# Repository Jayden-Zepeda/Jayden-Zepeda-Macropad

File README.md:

# ZepedaPad

> A custom 14-key macropad with dual rotary encoders, per-key RGB lighting, and an OLED display — built on the Seeed XIAO RP2040 with QMK firmware.

---

## 📖 Overview

The **Zepeda** is a compact, handcrafted macropad designed for productivity and personalization. It features 14 MX-style switches arranged in a 3×4 grid (plus a dedicated column), two EC11 rotary encoders for scrolling or volume control, individually addressable SK6812 MINI-E RGB LEDs under every key, and a 0.91" OLED display for live feedback — all driven by a Seeed XIAO RP2040 and QMK firmware.

The key matrix is read through a **74HC165 shift register**, keeping GPIO usage minimal while supporting full anti-ghosting via 1N4148 diodes. The entire build fits inside a custom 3-part 3D-printed case secured with heatset inserts and M3 screws.

PCB is designed through KICAD and the case is designed in Autodesk Fusion-FREE.

---

## 🖼️ Screenshots

### 3D Render

<p align="center">
  
  <br/><em>Top-down view</em>
</p>

<p align="center">
  
  <br/><em>Isometric view showing case depth and USB cutout</em>
</p>

---

### Schematic

> Full schematic showing the XIAO RP2040, 74HC165 shift register, LED chain, diode matrix, rotary encoders, and OLED connector.

<p align="center">
  
  <br/><em>KiCad schematic — macropad.kicad_sch</em>
</p>

---

### PCB Layout

<p align="center">
  
  <br/><em>KiCad PCB layout — red/blue layers, switch footprints, and LED positions visible</em>
</p>

---

### Case

<p align="center">
  
  <br/><em>3-part 3D-printed enclosure with heatset inserts. The PCB sits inside the bottom shell; the top plate exposes keycaps, encoders, and the OLED. A middle layer sandwiches everything together. Screws are enter from bottom, they go in 2mm freely and then left side screws all the way into the heatset insterts that are in the top shell while, the right side screws does a very similar thing except the heatset insterts are 1mm in the top shell and 3mm in the middle shell.</em>
</p>

The case consists of three printed parts(created in Autodesk Fusion-FREE) :
- **Bottom shell** — holds the PCB
- **Middle frame / plate** — key switch mounting plate
- **Top accent** — surrounds the OLED and encoder knobs

All three parts are secured with **4× M3×16mm screws** threading into **4× M3×5mm×4mm heatset inserts** pressed into the top/middle shell.

---

## 🧰 Bill of Materials (BOM)

| Qty | Part | Notes |
|-----|------|-------|
| 1 | Seeed XIAO RP2040 | Microcontroller (unsoldered) |
| 1 | 74HC165 Shift Register | Through-hole DIP-16 |
| 16 | SK6812 MINI-E LEDs | Per-key addressable RGB |
| 16 | 1N4148 Diodes | Through-hole, for key matrix |
| 14 | MX-Style Switches | Any MX-compatible switch |
| 14 | White Blank DSA Keycaps | 1u, blank |
| 2 | EC11 Rotary Encoders | With push-click |
| 1 | 0.91" OLED Display | I2C, SSD1306 |
| 1 | 3D-Printed Case | 3 printed parts |
| 4 | M3×16mm Screws | Case assembly |
| 4 | M3×5mm×4mm Heatset Inserts | Press-fit into top/middle shell |

---

## ⚡ Firmware

This macropad runs **QMK Firmware**. The 74HC165 shift register is used to read the key matrix, and the SK6812 MINI-E LEDs are driven via QMK's RGB Matrix feature. Created a full keyboard and keymap layout from scratch. Included in firmware folder(macropad).                                    

Features:
-Copy/Paste Key: First click is copy-second is paste, with an led and OLED display to show your status.
-Mute/Unmute Key: Led and OLED display to show your status
-4 Different Layers: Base, Media, Gaming, and CFG -- w/ led status

To build and flash:

```bash
qmk compile -kb macropad -km default
qmk flash -kb macropad -km default
```

Put the XIAO RP2040 into bootloader mode by holding **BOOT** while plugging in USB (or double-tapping RST).

---

## 🔧 Build Notes

- Solder **heatset inserts first** before assembling the case
- Flash QMK firmware onto the XIAO RP2040 **before** soldering it to the board
- The LED chain is daisy-chained: DOUT of each SK6812 connects to DIN of the next
- Diodes are oriented with the **cathode (K) toward the row line** — check markings before soldering
- The 74HC165's `~PL`, `CP`, and `Q7` lines connect to GPIO26, GPIO27, and GPIO28 on the XIAO respectively

---

## 📁 Repository Structure

```
Jayden-Zepeda-Macropad/
├── pcb/               # KiCad project files (.kicad_sch, .kicad_pcb)
├── case/              # 3D print files (.step / .stl)
├── firmware/          # QMK keymap and config
├── images/            # Images
├── production/            # Files for production
└── README.md
```

---

*Made with ❤️ as part of [Hack Club's PCB program](https://hackclub.com/)*

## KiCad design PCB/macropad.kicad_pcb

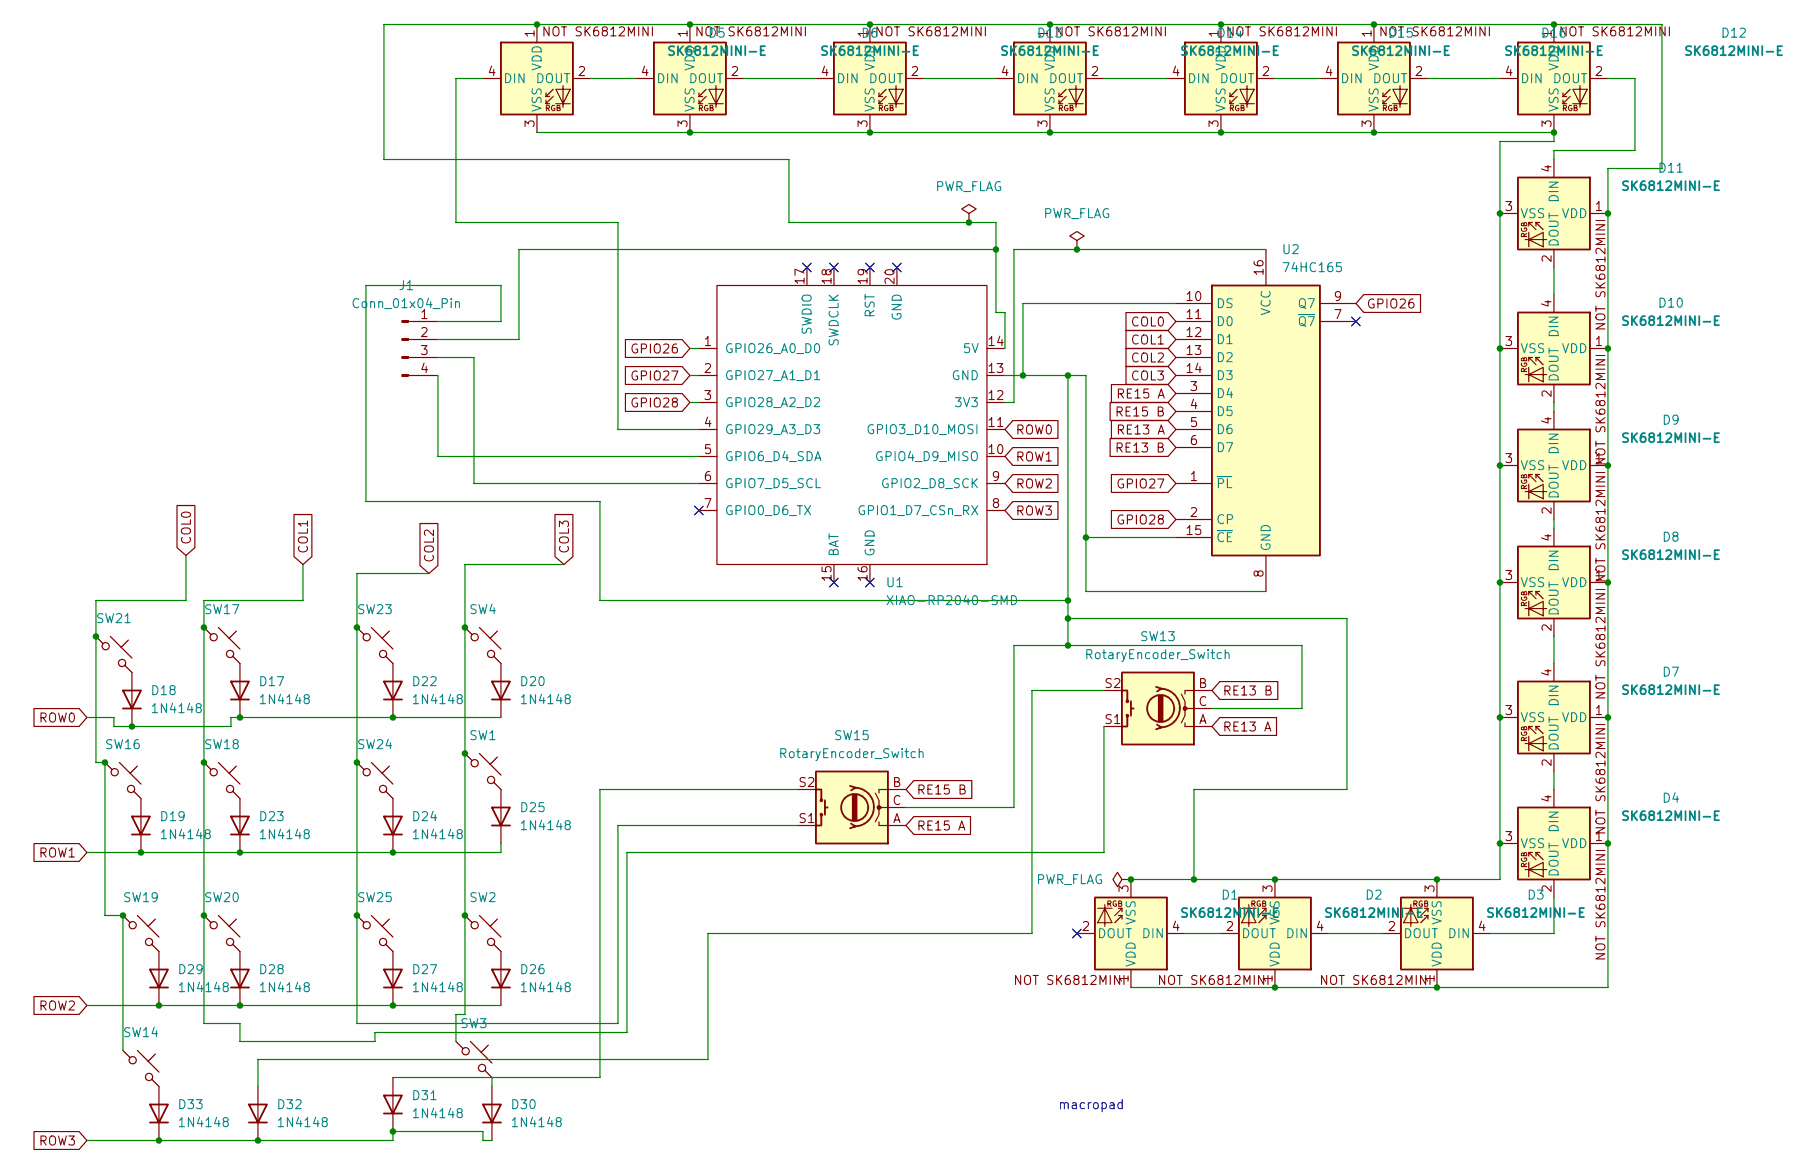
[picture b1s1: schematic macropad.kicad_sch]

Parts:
D1, D2, D3, D4, D5, D6, D7, D8, D9, D10, D11, D12, D13, D14, D15, D16: SK6812MINI-E; LED_SK6812MINI_PLCC4_3.5x3.5mm_P1.75mm
D17, D18, D19, D20, D22, D23, D24, D25, D26, D27, D28, D29, D30, D31, D32, D33: 1N4148; D_DO-35_SOD27_P7.62mm_Horizontal
J1: Conn_01x04_Pin; PinHeader_1x04_P2.54mm_Vertical
SW1, SW2, SW3, SW4, SW16, SW17, SW18, SW19, SW20, SW21, SW23, SW24, SW25: SW_Push_45deg; SW_Cherry_MX_1.00u_PCB
SW13, SW15: RotaryEncoder_Switch; RotaryEncoder_Alps_EC11E-Switch_Vertical_H20mm
SW14: SW_Push_45deg; SW_Cherry_MX_2.00u_PCB
U1: XIAO-RP2040-SMD; XIAO-RP2040-DIP
U2: 74HC165; DIP254P762X420-16

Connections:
COL0: SW14.1, SW16.1, SW19.1, SW21.1, U2.11 (D0)
COL1: SW13.S1, SW17.1, SW18.1, SW20.1, U2.12 (D1)
COL2: SW15.S1, SW23.1, SW24.1, SW25.1, U2.13 (D2)
COL3: SW1.1, SW2.1, SW3.1, SW4.1, U2.14 (D3)
GPIO26: U1.1 (GPIO26_A0_D0), U2.9 (Q7)
GPIO27: U1.2 (GPIO27_A1_D1), U2.1 (~PL)
GPIO28: U1.3 (GPIO28_A2_D2), U2.2 (CP)
unnamed: D1.4 (DIN), D2.2 (DOUT)
unnamed: D1.1 (VDD), D2.1 (VDD), D3.1 (VDD), D4.1 (VDD), D5.1 (VDD), D6.1 (VDD), D7.1 (VDD), D8.1 (VDD), D9.1 (VDD), D10.1 (VDD), D11.1 (VDD), D12.1 (VDD), D13.1 (VDD), D14.1 (VDD), D15.1 (VDD), D16.1 (VDD), J1.2, U1.14 (5V)
unnamed: D1.3 (VSS), D2.3 (VSS), D3.3 (VSS), D4.3 (VSS), D5.3 (VSS), D6.3 (VSS), D7.3 (VSS), D8.3 (VSS), D9.3 (VSS), D10.3 (VSS), D11.3 (VSS), D12.3 (VSS), D13.3 (VSS), D14.3 (VSS), D15.3 (VSS), D16.3 (VSS), J1.1, SW13.C, SW15.C, U1.13 (GND), U2.8 (GND), U2.10 (DS), U2.15 (~CE)
unnamed: D2.4 (DIN), D3.2 (DOUT)
unnamed: D3.4 (DIN), D4.2 (DOUT)
unnamed: D4.4 (DIN), D7.2 (DOUT)
unnamed: D5.4 (DIN), U1.4 (GPIO29_A3_D3)
unnamed: D5.2 (DOUT), D6.4 (DIN)
unnamed: D7.4 (DIN), D8.2 (DOUT)
unnamed: D8.4 (DIN), D9.2 (DOUT)
unnamed: D10.4 (DIN), D11.2 (DOUT)
unnamed: D9.4 (DIN), D10.2 (DOUT)
unnamed: D11.4 (DIN), D12.2 (DOUT)
unnamed: D12.4 (DIN), D16.2 (DOUT)
unnamed: D6.2 (DOUT), D13.4 (DIN)
unnamed: D13.2 (DOUT), D14.4 (DIN)
unnamed: D14.2 (DOUT), D15.4 (DIN)
unnamed: D15.2 (DOUT), D16.4 (DIN)
unnamed: D17.2 (A), SW17.2
unnamed: D18.2 (A), SW21.2
unnamed: D19.2 (A), SW16.2
unnamed: D20.2 (A), SW4.2
unnamed: D22.2 (A), SW23.2
unnamed: D23.2 (A), SW18.2
unnamed: D24.2 (A), SW24.2
unnamed: D25.2 (A), SW1.2
unnamed: D26.2 (A), SW2.2
unnamed: D27.2 (A), SW25.2
unnamed: D28.2 (A), SW20.2
unnamed: D29.2 (A), SW19.2
unnamed: D30.2 (A), SW3.2
unnamed: D31.2 (A), SW15.S2
unnamed: D32.2 (A), SW13.S2
unnamed: D33.2 (A), SW14.2
unnamed: J1.3, U1.6 (GPIO7_D5_SCL)
unnamed: J1.4, U1.5 (GPIO6_D4_SDA)
unnamed: U1.12 (3V3), U2.16 (VCC)
RE13 A: SW13.A, U2.5 (D6)
RE13 B: SW13.B, U2.6 (D7)
RE15 A: SW15.A, U2.3 (D4)
RE15 B: SW15.B, U2.4 (D5)
ROW0: D17.1 (K), D18.1 (K), D20.1 (K), D22.1 (K), U1.11 (GPIO3_D10_MOSI)
ROW1: D19.1 (K), D23.1 (K), D24.1 (K), D25.1 (K), U1.10 (GPIO4_D9_MISO)
ROW2: D26.1 (K), D27.1 (K), D28.1 (K), D29.1 (K), U1.9 (GPIO2_D8_SCK)
ROW3: D30.1 (K), D31.1 (K), D32.1 (K), D33.1 (K), U1.8 (GPIO1_D7_CSn_RX)

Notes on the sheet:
macropad

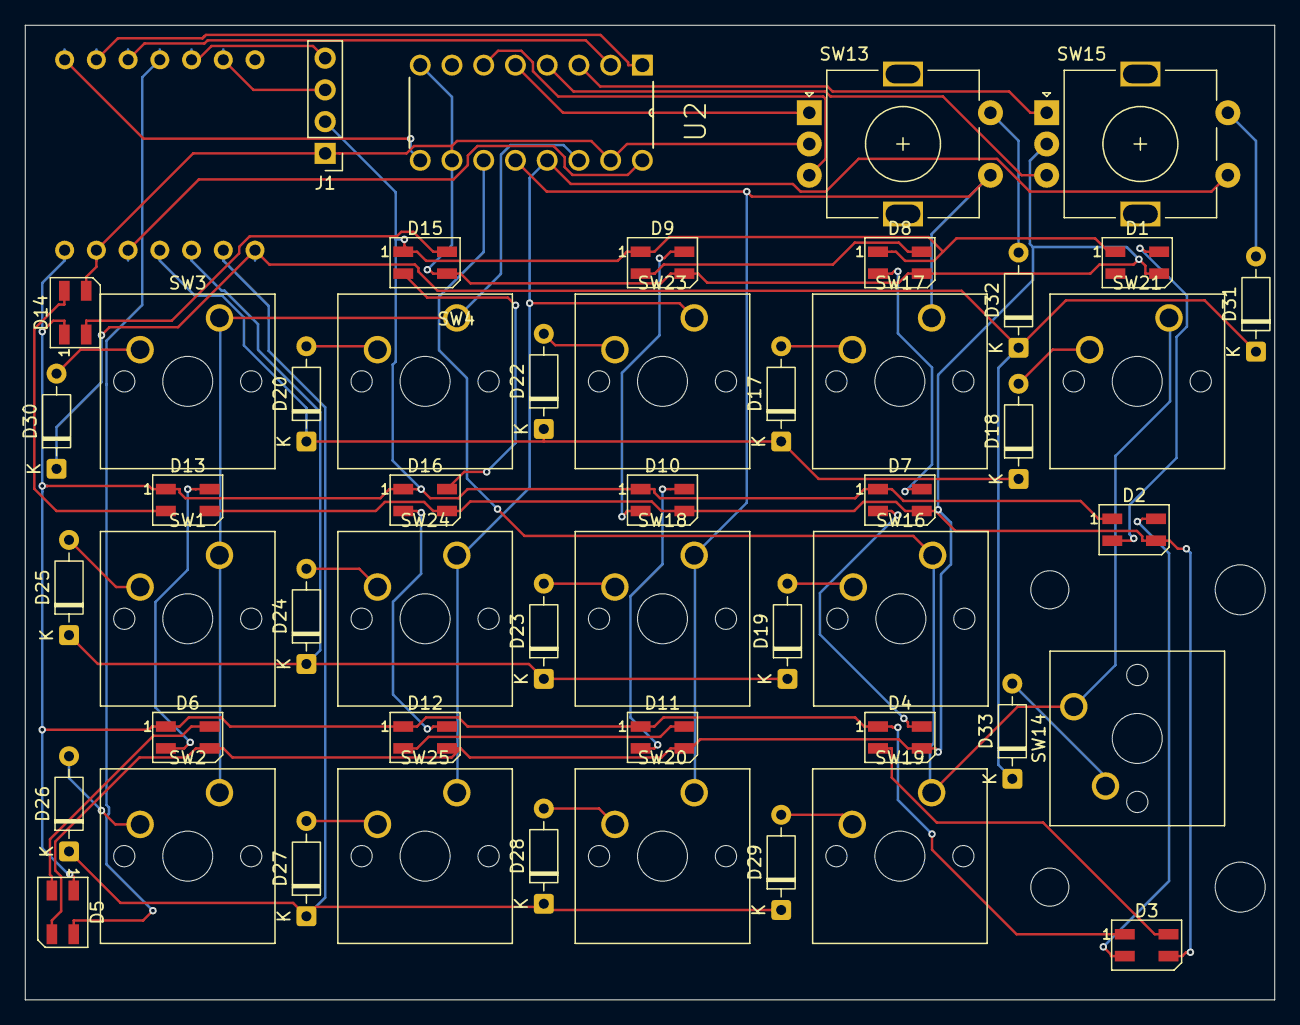
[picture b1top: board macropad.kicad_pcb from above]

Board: 2 copper layers, 100.0 x 78.0 mm, 51 parts (1 on the bottom side), 52 nets.

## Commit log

2026-03-30 Firmware and Production is left
2026-03-30 Almost done- REVIEW NEEDED
2026-03-31 CHECK NEEDED
2026-03-31 Images/README
2026-03-31 Review
2026-03-31 Final
